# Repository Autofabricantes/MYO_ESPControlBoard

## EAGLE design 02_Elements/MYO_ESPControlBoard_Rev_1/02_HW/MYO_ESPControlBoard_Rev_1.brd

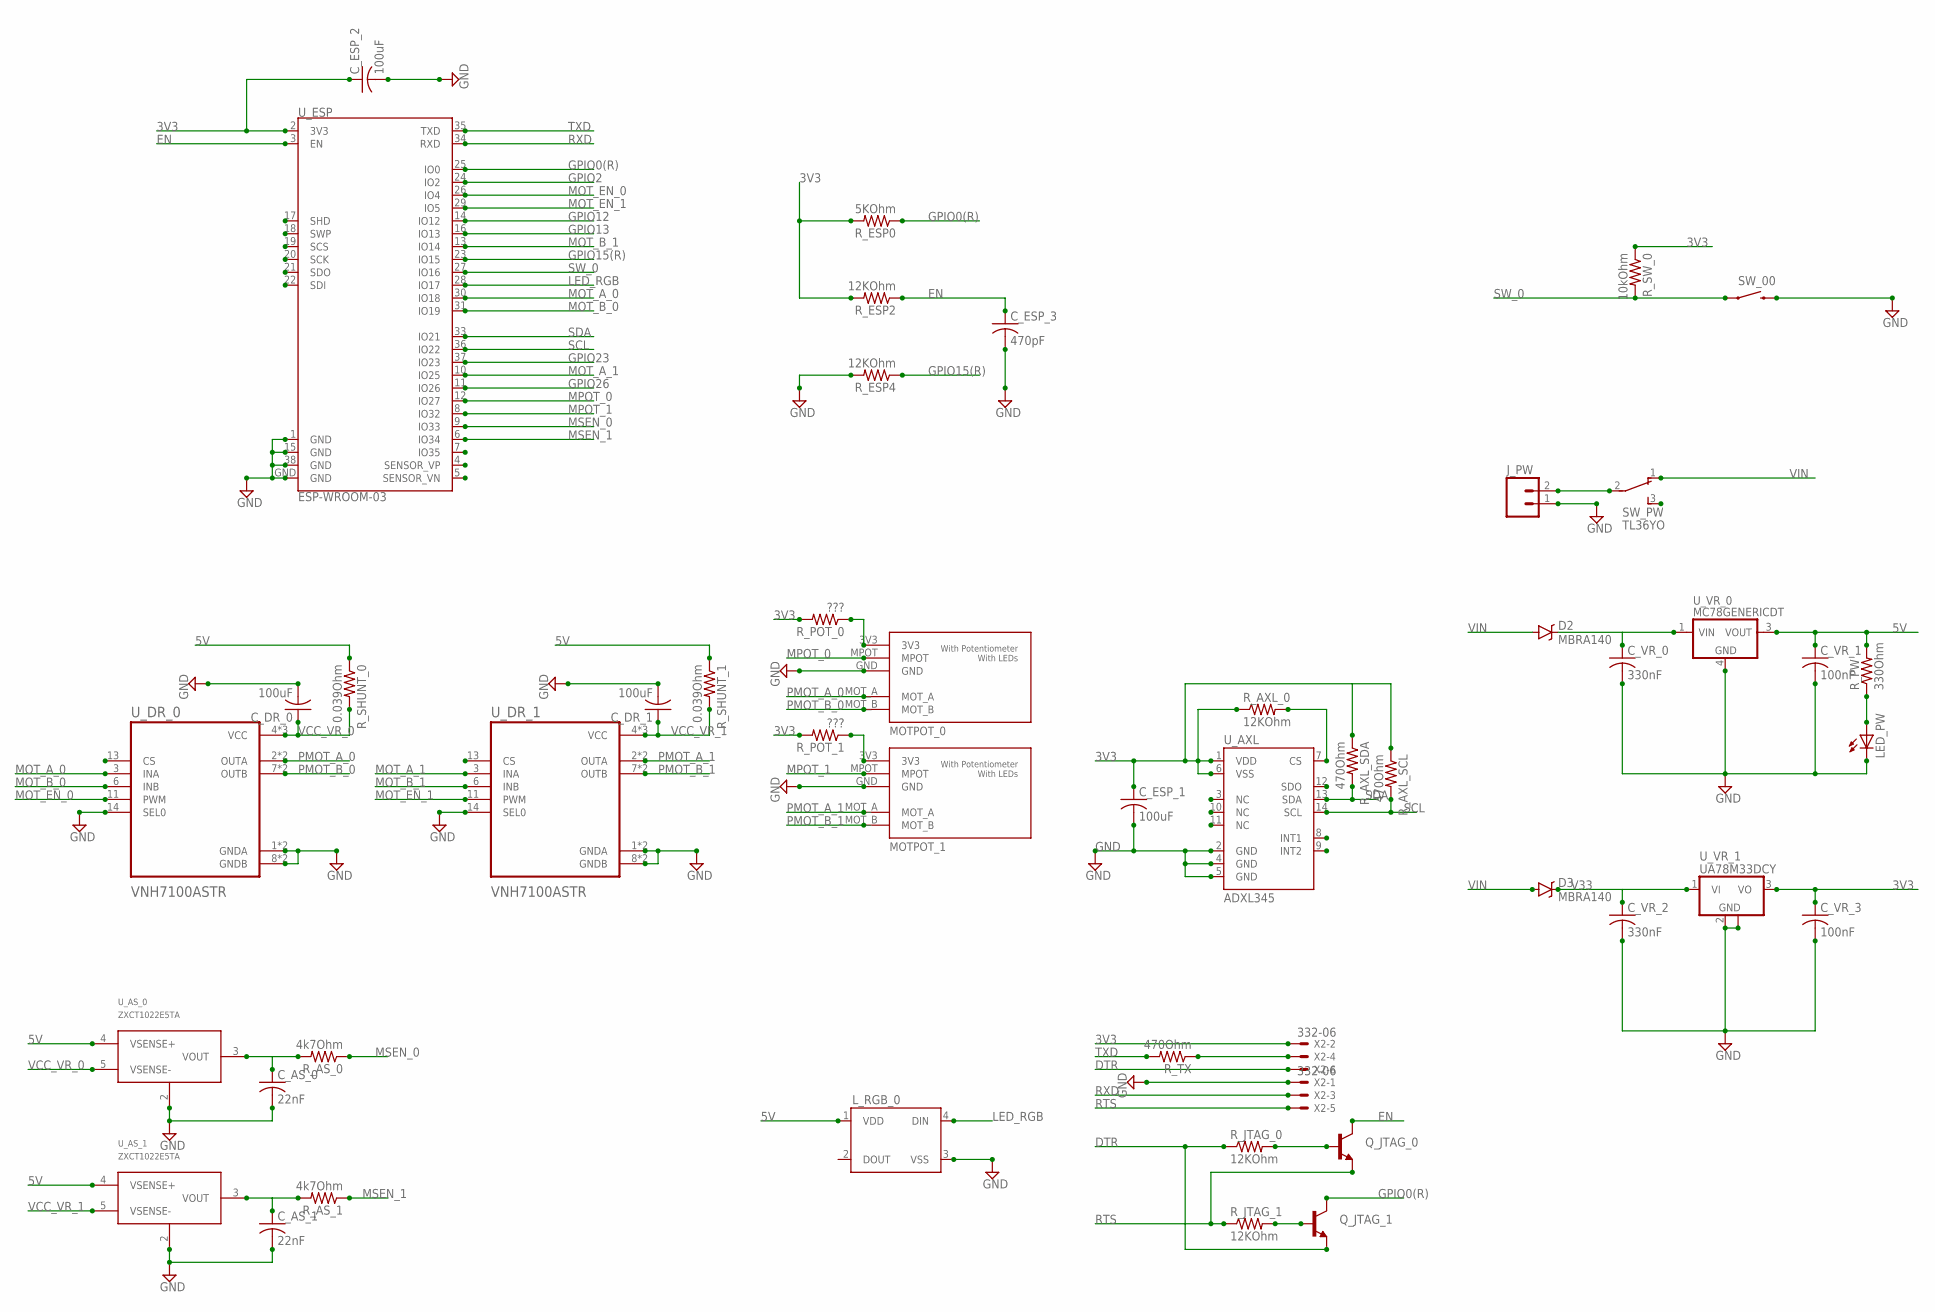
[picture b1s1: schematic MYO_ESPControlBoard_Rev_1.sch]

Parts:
C_AS_0, C_AS_1: 22nF; C0805K
C_DR_0, C_DR_1: 100uF; C0805K
C_ESP_1, C_ESP_2: 100uF; C0805K
C_ESP_3: 470pF; C0805K
C_VR_0, C_VR_2: 330nF; C0805
C_VR_1, C_VR_3: 100nF; C0805
D2, D3: MBRA140; SMA-DIODE
J_PW: M02-JST-2MM-SMT; JST-2-SMD
LED_PW: LEDSMT1206; 1206
L_RGB_0: WS2812B
MOTPOT_0, MOTPOT_1: POLOLU_MOT_POT
Q_JTAG_0, Q_JTAG_1: TRANSISTOR_NPNSOT23-3; SOT23-3
R_AS_0, R_AS_1: 4k7Ohm; M0805
R_AXL_0: 12KOhm; M0805
R_AXL_SCL: 470Ohm; M0805
R_AXL_SDA: 470Ohm; M0805
R_ESP0: 5KOhm; M0805
R_ESP2, R_ESP4: 12KOhm; M0805
R_JTAG_0, R_JTAG_1: 12KOhm; M0805
R_POT_0, R_POT_1: ???; M0805
R_PW: 330Ohm; M0805
R_SHUNT_0, R_SHUNT_1: 0.039Ohm; M0805
R_SW_0: 10kOhm; M0805
R_TX: 470Ohm; M0805
SW_00: SWITCH-MOMENTARY-2TACTILE-SWITCH-SMD-RIGHT-ANGLE; TACTILE_SWITCH-SMD-RIGHT-ANGLE
SW_PW: TL36YO; TL3XYO
U_AS_0, U_AS_1: ZXCT1022E5TA; SOT95P270X145-5N(SOT23-5)
U_AXL: ADXL345; LGA14
U_DR_0, U_DR_1: VNH7100ASTR; SOIC127P600X175-16N
U_ESP: ESP-WROOM-03
U_VR_0: MC78GENERICDT; DPAK-3
U_VR_1: UA78M33DCY; SOT223
X2: 332-06

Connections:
3V3: C_ESP_1.1, C_ESP_2.1, C_VR_3.1, R_AXL_0.1, R_AXL_SCL.1, R_AXL_SDA.1, R_ESP0.2, R_ESP2.2, R_POT_0.2, R_POT_1.2, R_SW_0.1, U_AXL.1 (VDD), U_AXL.6 (VSS), U_ESP.2 (3V3), U_VR_1.3 (VO), X2.2
5V: C_VR_1.1, L_RGB_0.1 (VDD), R_PW.2, R_SHUNT_0.1, R_SHUNT_1.1, U_AS_0.4 (VSENSE+), U_AS_1.4 (VSENSE+), U_VR_0.3 (VOUT)
DTR: Q_JTAG_1.2 (E), R_JTAG_0.1, X2.6
EN: C_ESP_3.1, Q_JTAG_0.3 (C), R_ESP2.1, U_ESP.3 (EN)
GND: C_AS_0.2, C_AS_1.2, C_DR_0.2, C_DR_1.2, C_ESP_1.2, C_ESP_2.2, C_ESP_3.2, C_VR_0.2, C_VR_1.2, C_VR_2.2, C_VR_3.2, J_PW.1, LED_PW.C, L_RGB_0.3 (VSS), MOTPOT_0.GND, MOTPOT_1.GND, R_ESP4.2, SW_00.2, U_AS_0.2 (GND), U_AS_1.2 (GND), U_AXL.2 (GND), U_AXL.4 (GND), U_AXL.5 (GND), U_DR_0.1 (GNDA), U_DR_0.8 (GNDB), U_DR_0.9 (GNDB), U_DR_0.14 (SEL0), U_DR_0.16 (GNDA), U_DR_1.1 (GNDA), U_DR_1.8 (GNDB), U_DR_1.9 (GNDB), U_DR_1.14 (SEL0), U_DR_1.16 (GNDA), U_ESP.1 (GND), U_ESP.15 (GND), U_ESP.38 (GND), U_ESP.GND, U_VR_0.4 (GND), U_VR_1.2 (GND), U_VR_1.4 (GND), X2.1
GPIO0(R): Q_JTAG_1.3 (C), R_ESP0.1, U_ESP.25 (IO0)
GPIO2: U_ESP.24 (IO2)
GPIO12: U_ESP.14 (IO12)
GPIO13: U_ESP.16 (IO13)
GPIO15(R): R_ESP4.1, U_ESP.23 (IO15)
GPIO23: U_ESP.37 (IO23)
GPIO26: U_ESP.11 (IO26)
LED_RGB: L_RGB_0.4 (DIN), U_ESP.28 (IO17)
MOT_A_0: U_DR_0.3 (INA), U_ESP.30 (IO18)
MOT_A_1: U_DR_1.3 (INA), U_ESP.10 (IO25)
MOT_B_0: U_DR_0.6 (INB), U_ESP.31 (IO19)
MOT_B_1: U_DR_1.6 (INB), U_ESP.13 (IO14)
MOT_EN_0: U_DR_0.11 (PWM), U_ESP.26 (IO4)
MOT_EN_1: U_DR_1.11 (PWM), U_ESP.29 (IO5)
MPOT_0: MOTPOT_0.MPOT, U_ESP.12 (IO27)
MPOT_1: MOTPOT_1.MPOT, U_ESP.8 (IO32)
MSEN_0: R_AS_0.1, U_ESP.9 (IO33)
MSEN_1: R_AS_1.1, U_ESP.6 (IO34)
unnamed: MOTPOT_0.3V3, R_POT_0.1
unnamed: MOTPOT_1.3V3, R_POT_1.1
unnamed: Q_JTAG_0.1 (B), R_JTAG_0.2
unnamed: LED_PW.A, R_PW.1
unnamed: Q_JTAG_1.1 (B), R_JTAG_1.2
unnamed: R_TX.1, X2.4
unnamed: C_AS_0.1, R_AS_0.2, U_AS_0.3 (VOUT)
unnamed: R_AXL_0.2, U_AXL.7 (CS)
unnamed: J_PW.2, SW_PW.2
unnamed: C_AS_1.1, R_AS_1.2, U_AS_1.3 (VOUT)
PMOT_A_0: MOTPOT_0.MOT_A, U_DR_0.2 (OUTA), U_DR_0.15 (OUTA)
PMOT_A_1: MOTPOT_1.MOT_A, U_DR_1.2 (OUTA), U_DR_1.15 (OUTA)
PMOT_B_0: MOTPOT_0.MOT_B, U_DR_0.7 (OUTB), U_DR_0.10 (OUTB)
PMOT_B_1: MOTPOT_1.MOT_B, U_DR_1.7 (OUTB), U_DR_1.10 (OUTB)
RTS: Q_JTAG_0.2 (E), R_JTAG_1.1, X2.5
RXD: U_ESP.34 (RXD), X2.3
SCL: R_AXL_SCL.2, U_AXL.14 (SCL), U_ESP.36 (IO22)
SDA: R_AXL_SDA.2, U_AXL.13 (SDA), U_ESP.33 (IO21)
SW_0: R_SW_0.2, SW_00.1, U_ESP.27 (IO16)
TXD: R_TX.2, U_ESP.35 (TXD)
V5: C_VR_0.1, D2.C, U_VR_0.1 (VIN)
V33: C_VR_2.1, D3.C, U_VR_1.1 (VI)
VCC_VR_0: C_DR_0.1, R_SHUNT_0.2, U_AS_0.5 (VSENSE-), U_DR_0.4 (VCC), U_DR_0.5 (VCC), U_DR_0.12 (VCC)
VCC_VR_1: C_DR_1.1, R_SHUNT_1.2, U_AS_1.5 (VSENSE-), U_DR_1.4 (VCC), U_DR_1.5 (VCC), U_DR_1.12 (VCC)
VIN: D2.A, D3.A, SW_PW.1 (O)

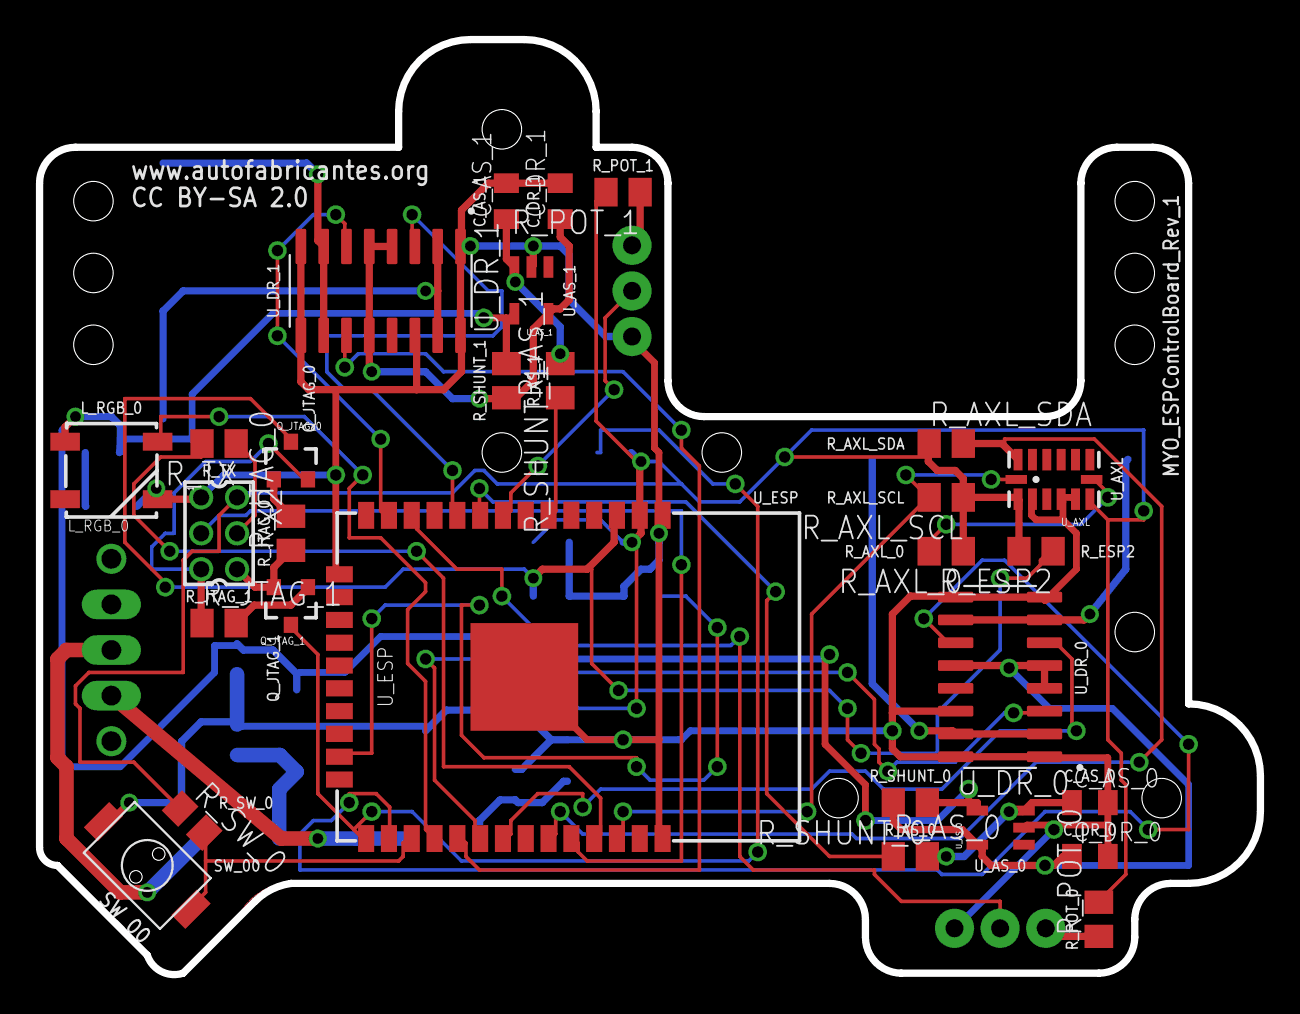
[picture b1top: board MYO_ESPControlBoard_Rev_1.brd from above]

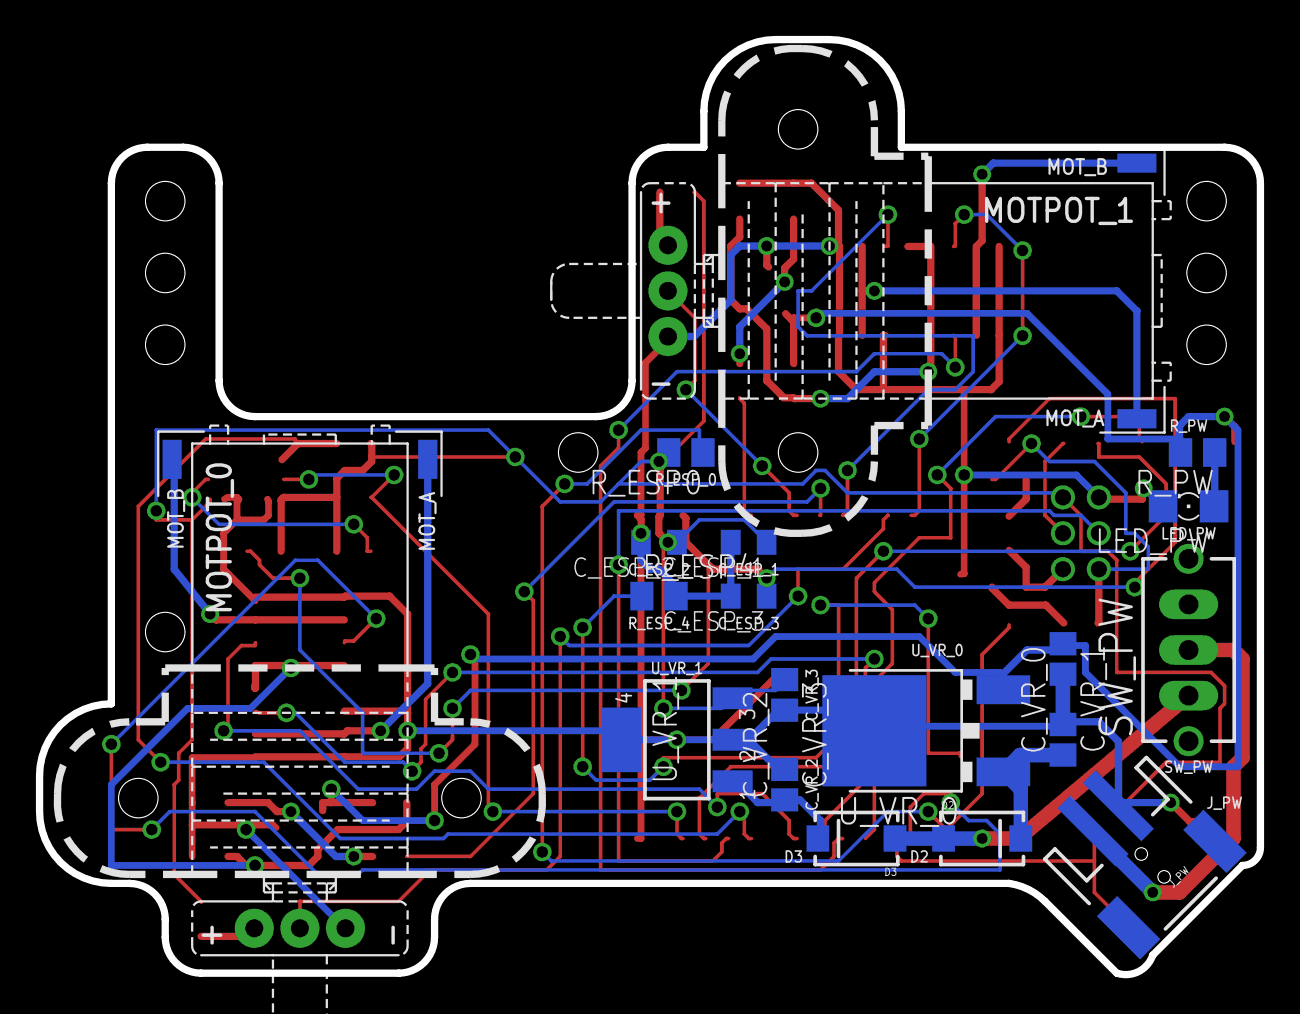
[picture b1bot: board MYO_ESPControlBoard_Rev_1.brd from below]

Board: 2 copper layers, 68.0 x 52.1 mm, 48 parts (19 on the bottom side), 43 nets.

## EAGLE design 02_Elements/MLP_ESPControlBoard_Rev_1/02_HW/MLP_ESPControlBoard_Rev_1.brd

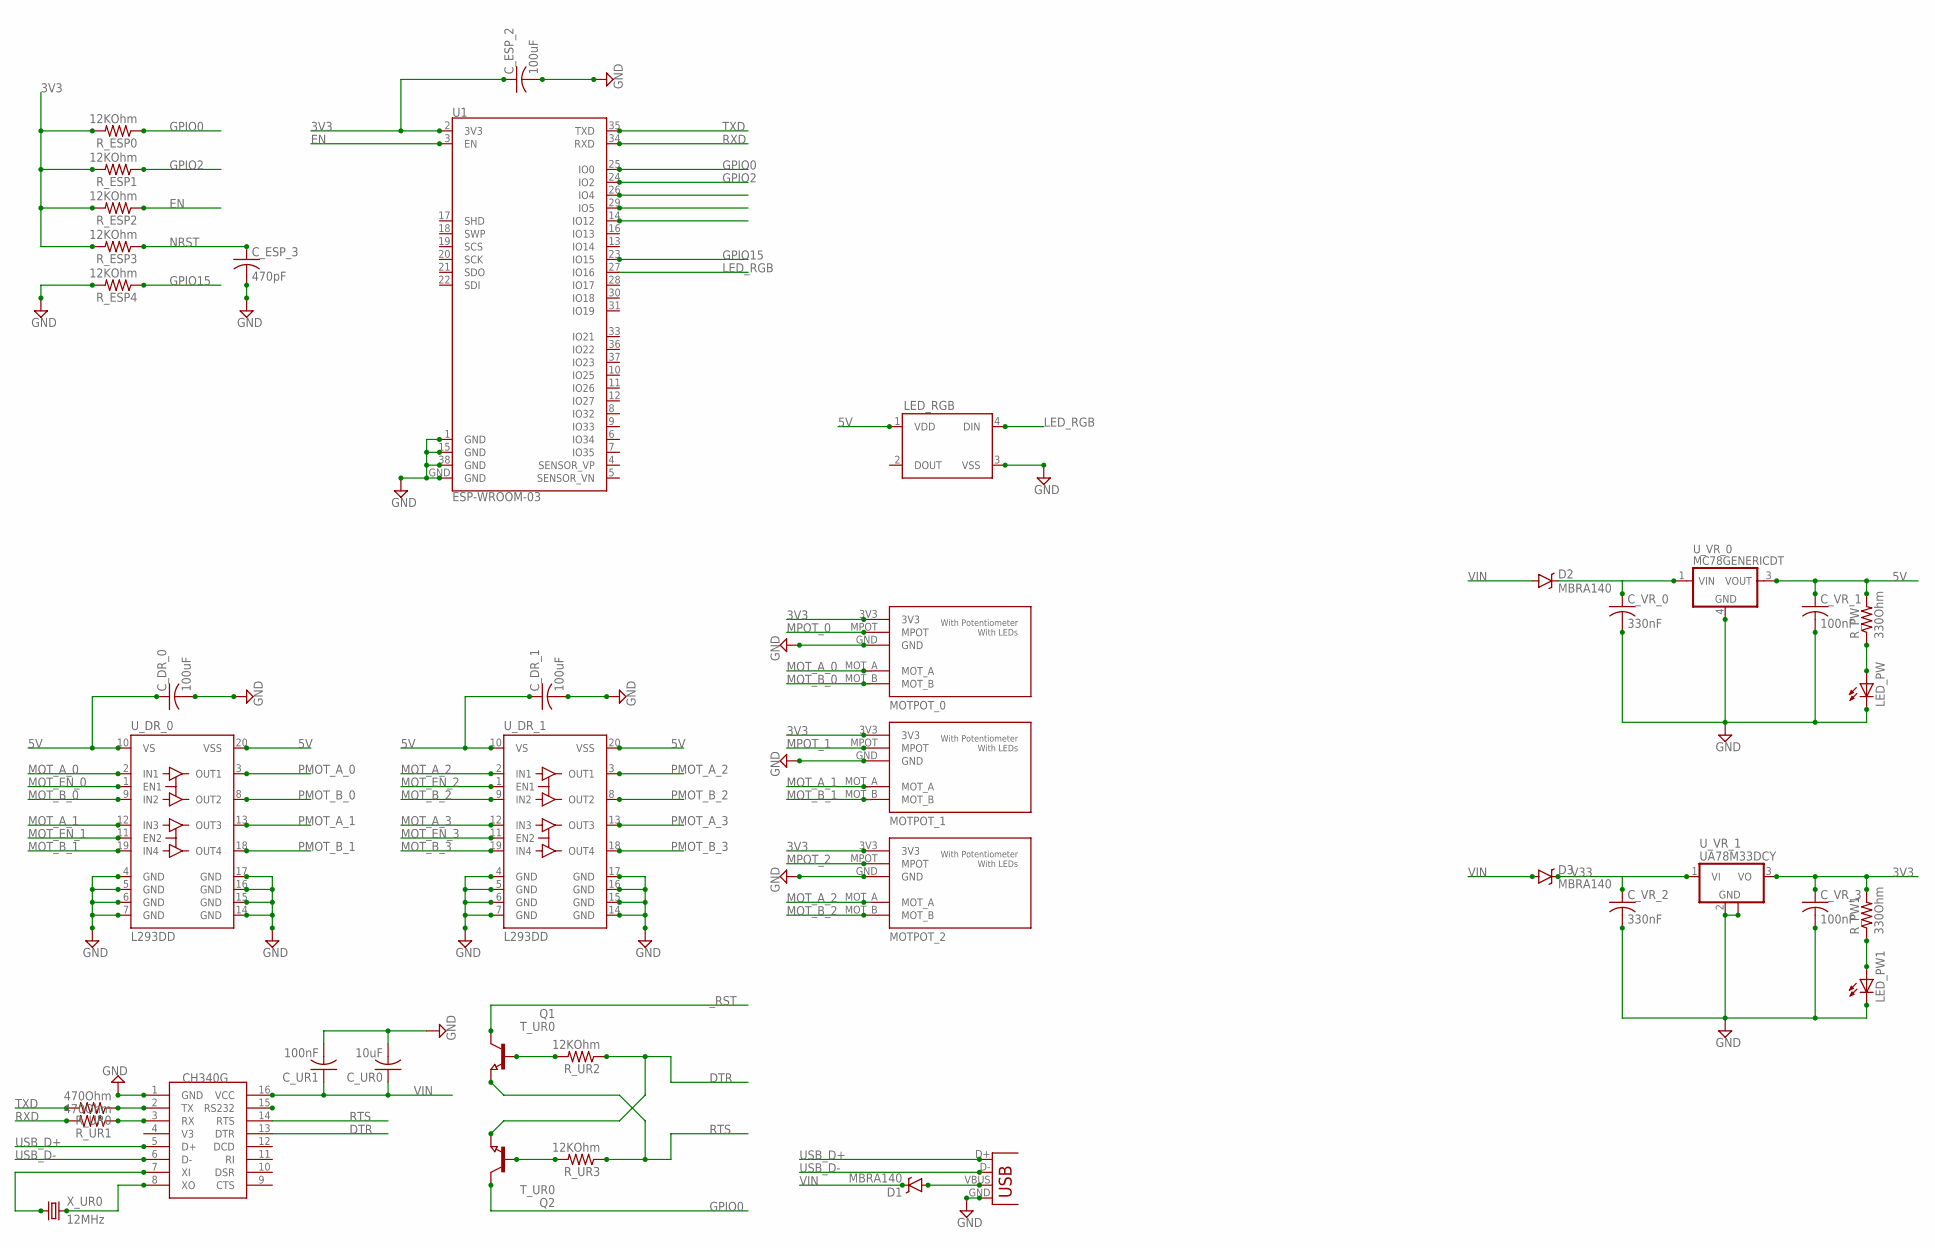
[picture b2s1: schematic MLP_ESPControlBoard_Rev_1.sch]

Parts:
C_DR_0, C_DR_1: 100uF; C0805K
C_ESP_2: 100uF; C0805K
C_ESP_3: 470pF; C0805K
C_UR0: 10uF; C0805K
C_UR1: 100nF; C0805K
C_VR_0, C_VR_2: 330nF; C1206K
C_VR_1, C_VR_3: 100nF; C1206K
D1, D2, D3: MBRA140; SMA-DIODE
LED_PW, LED_PW1: LEDSMT1206; 1206
LED_RGB: WS2812B
MOTPOT_0, MOTPOT_1, MOTPOT_2: POLOLU_MOT_POT
Q1, Q2: T_UR0; SOT23
R_ESP0, R_ESP1, R_ESP2, R_ESP3, R_ESP4: 12KOhm; M0805
R_PW, R_PW1: 330Ohm; M1206
R_UR0, R_UR1: 470Ohm; M1206
R_UR2, R_UR3: 12KOhm; M1206
U1: ESP-WROOM-03
U_DR_0, U_DR_1: L293DD; SO20
U_UR0: CH340G; SOIC16
U_VR_0: MC78GENERICDT; DPAK-3
U_VR_1: UA78M33DCY; SOT223
X1: USB-MICROB
X_UR0: 12MHz; CTS406

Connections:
3V3: C_ESP_2.1, C_VR_3.1, MOTPOT_0.3V3, MOTPOT_1.3V3, MOTPOT_2.3V3, R_ESP0.2, R_ESP1.2, R_ESP2.2, R_ESP3.2, R_PW1.2, U1.2 (3V3), U_VR_1.3 (VO)
5V: C_DR_0.1, C_DR_1.1, C_VR_1.1, LED_RGB.1 (VDD), R_PW.2, U_DR_0.10 (VS), U_DR_0.20 (VSS), U_DR_1.10 (VS), U_DR_1.20 (VSS), U_VR_0.3 (VOUT)
DTR: Q2.2 (E), R_UR2.1, U_UR0.13 (DTR)
EN: R_ESP2.1, U1.3 (EN)
GND: C_DR_0.2, C_DR_1.2, C_ESP_2.2, C_ESP_3.2, C_UR0.2, C_UR1.2, C_VR_0.2, C_VR_1.2, C_VR_2.2, C_VR_3.2, LED_PW.C, LED_PW1.C, LED_RGB.3 (VSS), MOTPOT_0.GND, MOTPOT_1.GND, MOTPOT_2.GND, R_ESP4.2, U1.1 (GND), U1.15 (GND), U1.38 (GND), U1.GND, U_DR_0.4 (GND), U_DR_0.5 (GND), U_DR_0.6 (GND), U_DR_0.7 (GND), U_DR_0.14 (GND), U_DR_0.15 (GND), U_DR_0.16 (GND), U_DR_0.17 (GND), U_DR_1.4 (GND), U_DR_1.5 (GND), U_DR_1.6 (GND), U_DR_1.7 (GND), U_DR_1.14 (GND), U_DR_1.15 (GND), U_DR_1.16 (GND), U_DR_1.17 (GND), U_UR0.1 (GND), U_VR_0.4 (GND), U_VR_1.2 (GND), U_VR_1.4 (GND), X1.GND
GPIO0: Q2.3 (C), R_ESP0.1, U1.25 (IO0)
GPIO2: R_ESP1.1, U1.24 (IO2)
GPIO15: R_ESP4.1, U1.23 (IO15)
LED_RGB: LED_RGB.4 (DIN), U1.27 (IO16)
MOT_A_0: MOTPOT_0.MOT_A, U_DR_0.2 (IN1)
MOT_A_1: MOTPOT_1.MOT_A, U_DR_0.12 (IN3)
MOT_A_2: MOTPOT_2.MOT_A, U_DR_1.2 (IN1)
MOT_A_3: U_DR_1.12 (IN3)
MOT_B_0: MOTPOT_0.MOT_B, U_DR_0.9 (IN2)
MOT_B_1: MOTPOT_1.MOT_B, U_DR_0.19 (IN4)
MOT_B_2: MOTPOT_2.MOT_B, U_DR_1.9 (IN2)
MOT_B_3: U_DR_1.19 (IN4)
MOT_EN_0: U_DR_0.1 (EN1)
MOT_EN_1: U_DR_0.11 (EN2)
MOT_EN_2: U_DR_1.1 (EN1)
MOT_EN_3: U_DR_1.11 (EN2)
MPOT_0: MOTPOT_0.MPOT
MPOT_1: MOTPOT_1.MPOT
MPOT_2: MOTPOT_2.MPOT
unnamed: Q2.1 (B), R_UR3.2
unnamed: Q1.1 (B), R_UR2.2
unnamed: LED_PW.A, R_PW.1
unnamed: U_UR0.7 (XI), X_UR0.1
unnamed: LED_PW1.A, R_PW1.1
unnamed: R_UR0.1, U_UR0.2 (TX)
unnamed: R_UR1.1, U_UR0.3 (RX)
unnamed: U_UR0.8 (XO), X_UR0.3 (2)
unnamed: D1.A, X1.VBUS
NRST: C_ESP_3.1, R_ESP3.1
PMOT_A_0: U_DR_0.3 (OUT1)
PMOT_A_1: U_DR_0.13 (OUT3)
PMOT_A_2: U_DR_1.3 (OUT1)
PMOT_A_3: U_DR_1.13 (OUT3)
PMOT_B_0: U_DR_0.8 (OUT2)
PMOT_B_1: U_DR_0.18 (OUT4)
PMOT_B_2: U_DR_1.8 (OUT2)
PMOT_B_3: U_DR_1.18 (OUT4)
RTS: Q1.2 (E), R_UR3.1, U_UR0.14 (RTS)
RXD: R_UR1.2, U1.34 (RXD)
TXD: R_UR0.2, U1.35 (TXD)
USB_D+: U_UR0.5 (D+), X1.D+
USB_D-: U_UR0.6 (D-), X1.D-
V5: C_VR_0.1, D2.C, U_VR_0.1 (VIN)
V33: C_VR_2.1, D3.C, U_VR_1.1 (VI)
VIN: C_UR0.1, C_UR1.1, D1.C, D2.A, D3.A, U_UR0.16 (VCC)
_RST: Q1.3 (C)

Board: 2 copper layers, 40 parts (0 on the bottom side), 33 nets, no tracks yet.

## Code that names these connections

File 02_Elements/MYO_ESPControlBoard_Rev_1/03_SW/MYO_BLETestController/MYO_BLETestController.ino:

/*  MYO_BLETestController
 * 
 * 
 * 
 */

#include <driver/dac.h>
#include "BluetoothSerial.h"
#include "MYO_Motor.h"
#include "MYO_LED.h"
#include <Adafruit_NeoPixel.h>
#ifdef __AVR__
 #include <avr/power.h> // Required for 16 MHz Adafruit Trinket
#endif

// Pin Definition
#define MOT_EN_0    4   // GPIO 4
#define MOT_A_0     18  // GPIO 18
#define MOT_B_0     19  // GPIO 19
#define MPOT_0      27  // GPIO 27
#define MSEN_0      33  // GPIO 33

#define MOT_EN_1    5   // GPIO 5
#define MOT_A_1     25  // GPIO 25
#define MOT_B_1     13  // GPIO 13 // GPIO14 in BRD. Changed due to Initial PWM Signal during BOOT
#define MPOT_1      32  // GPIO 32
#define MSEN_1      34  // GPIO 34

#define SW_0        16  // GPIO 16

#define LED_RGB     17  // GPIO17

BluetoothSerial SerialBT;
MYO_LED   LED(LED_RGB);
MYO_Motor MOT_0(MOT_EN_0, MOT_A_0, MOT_B_0, MPOT_0, MSEN_0);
MYO_Motor MOT_1(MOT_EN_1, MOT_A_1, MOT_B_1, MPOT_1, MSEN_1);

void readSerialCommand(){
    if (SerialBT.available()) {
      //String value =  SerialBT.read());
      String serialMessage = SerialBT.readString();
      if (serialMessage.length() > 0) {
        SerialBT.print("CMD Recieved: ");
        for (int i = 0; i < serialMessage.length(); i++){
          SerialBT.print(serialMessage[i]);
          
        }
        //SerialBT.println("");
        if(((serialMessage[0] == 'A')||(serialMessage[0] == 'B')) && (serialMessage.length()==7)){
          if(serialMessage[1] == 'P'){
            readCommandForMotorPosition(serialMessage);
          }else if(serialMessage[1] == 'S'){
            readCommandForMotorSpeed(serialMessage);
          }  
        }else if(serialMessage.substring(0,4).equals("STOP")){
          LED.fadeColor(BLUE_LOW, BLUE_HIGH, 500);
          MOT_0.stopLiberate();
          MOT_1.stopLiberate();
          LED.fadeColor(BLUE_LOW, BLUE_HIGH, 500);
        }else{
          SerialBT.println("Message Not Supported");
          LED.fadeColor(RED_LOW, RED_HIGH, 500);
        }
      }
    }
};

void setup() {
  LED.init();
  LED.setColor(CYAN_LOW);
  MOT_0.stopLiberate();
  MOT_1.stopLiberate();
  MOT_0.goToPosition(5);
  MOT_1.goToPosition(5);
  
  Serial.begin(9600); 
  SerialBT.begin("MYO_ATF"); //Bluetooth device name
  Serial.println("Waiting a client connection to notify...");
}

void loop() {
  // put your main code here, to run repeatedly:
  readSerialCommand();
  delay(10);
}

void readCommandForMotorPosition(String serialMessage){
  // First Check the message is correct (supported values between 0 and 100
  if(((serialMessage[2]== '0') || (serialMessage[2]== '1')) &&
     (((serialMessage[3]>= '0') && (serialMessage[3] <= '9')) &&
     ((serialMessage[4]>= '0') && (serialMessage[4] <= '9')))){
        int aimedPosition = (serialMessage[2] - 48)*100 + (serialMessage[3] - 48)*10 + (serialMessage[4] - 48)*1;
        if(aimedPosition > 100){
          aimedPosition = 100;
        }
        if(serialMessage[0] == 'A'){
          SerialBT.print("Motor A to position: ");
          SerialBT.println(aimedPosition);
          LED.fadeColor(BLUE_LOW, BLUE_HIGH, 500);
          MOT_0.goToPosition(map(aimedPosition, 0, 100, 5, 95));
        }else{
          SerialBT.print("Motor B to position: ");
          SerialBT.println(aimedPosition);
          LED.fadeColor(BLUE_LOW, BLUE_HIGH, 500);
          MOT_1.goToPosition(map(aimedPosition, 0, 100, 5, 95));
        }
  }else{
    SerialBT.print("Serial Message Incorrect: ");
    SerialBT.print(serialMessage);
    SerialBT.println(" .Use a notation with APXXX o BPXXX with values 000-100");
    LED.fadeColor(RED_LOW, RED_HIGH, 500);
  }
}

void readCommandForMotorSpeed(String serialMessage){
    // First Check the message is correct (supported values between 0 and 100
  if(((serialMessage[2]== '0') || (serialMessage[2]== '1')) &&
     (((serialMessage[3]>= '0') && (serialMessage[3] <= '9')) &&
     ((serialMessage[4]>= '0') && (serialMessage[4] <= '9')))){
        int aimedSpeed = (serialMessage[2] - 48)*100 + (serialMessage[3] - 48)*10 + (serialMessage[4] - 48)*1;
        if(aimedSpeed > 100){
          aimedSpeed = 100;
        }
        if(serialMessage[0] == 'A'){
          SerialBT.print("Motor A to speed: ");
          SerialBT.println(aimedSpeed);
          LED.fadeColor(TURQOUISE_LOW, TURQOUISE_HIGH, 500);
          MOT_0.setMotorSpeed(aimedSpeed);
        }else{
          SerialBT.print("Motor B to speed: ");
          SerialBT.println(aimedSpeed);
          LED.fadeColor(TURQOUISE_LOW, TURQOUISE_HIGH, 500);
          MOT_1.setMotorSpeed(aimedSpeed);
        }
  }else{
    SerialBT.print("Serial Message Incorrect: ");
    SerialBT.print(serialMessage);
    SerialBT.println(" .Use a notation with ASXXX o BSXXX with values 000-100");
    LED.fadeColor(RED_LOW, RED_HIGH, 500);
  }
}

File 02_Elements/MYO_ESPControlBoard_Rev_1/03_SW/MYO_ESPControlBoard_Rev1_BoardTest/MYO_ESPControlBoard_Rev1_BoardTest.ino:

#include <Adafruit_NeoPixel.h>

// Pin Definition
const int pMOT_EN_0     = 4;
const int pMOT_A_0      = 18;
const int pMOT_B_0      = 19;
const int pMPOT_0       = 27;

const int pMOT_EN_1     = 5;
const int pMOT_A_1      = 25;
const int pMOT_B_1      = 14;
const int pMPOT_1       = 32;

const int pMSEN_0       = 12;
const int pMSEN_1       = 33;

const int pLED_RGB      = 17;

const int pSW_0         = 16;

const int pSDA          = 21;
const int pSCL          = 22;


Adafruit_NeoPixel ledRGB = Adafruit_NeoPixel(1, pLED_RGB, NEO_RGB + NEO_KHZ800);

//Adafruit_NeoPixel pixels = Adafruit_NeoPixel(1, pLED_RGB, NEO_GRB + NEO_KHZ800);

bool memorySW = false;

void setup() {
  Serial.begin(115200);
  ledRGB.begin();
  ledRGB.setPixelColor(0, 255, 0, 255); // Moderately bright green color.
  ledRGB.show(); // This sends the updated pixel color to the hardware.
  delay(500); // Delay for a period of time (in milliseconds).
  pinMode(pMOT_EN_0,  OUTPUT);
  pinMode(pMOT_A_0,   OUTPUT);
  pinMode(pMOT_B_0,   OUTPUT);
  pinMode(pMOT_EN_1,  OUTPUT);
  pinMode(pMOT_A_1,   OUTPUT);
  pinMode(pMOT_B_1,   OUTPUT);
  pinMode(pSW_0,      INPUT);
  digitalWrite(pMOT_EN_0,  LOW);
  digitalWrite(pMOT_A_0,  LOW);
  digitalWrite(pMOT_B_0,  LOW);
  digitalWrite(pMOT_EN_1,  LOW);
  digitalWrite(pMOT_A_1,  LOW);
  digitalWrite(pMOT_B_1,  LOW);

}

void loop() {
  if(swActiveMomentary()){
    Serial.println("");
    Serial.println("PUSH!");
    ledRGB.setPixelColor(0, random(0,100), random(0,100), random(0,100)); // Moderately bright green color.
  }
  Serial.print(".");
  ledRGB.show(); // This sends the updated pixel color to the hardware.
  delay(10);
}

bool swActiveMomentary(){
  bool newSW = digitalRead(pSW_0);
  if((memorySW)&&(!newSW)){
    memorySW = newSW;
    return true;
  }else{
    memorySW = newSW;
    return false;
  }
}

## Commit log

2018-10-22 First Setup Folder
    First Simple Setup of the folder structure
2018-12-01 Beginning of Schematic Design
    Just temporary backup with circuits:
    - ESP32
    - Serial USB Comm
2019-01-23 Schematic Update
    Advanced Schematic, not final
2019-01-30 MYO_ESPControlBoard_Rev_1 Schematic completed
    Upload of the MYO_ESPControlBoard_Rev_1 Schematic to be tested
2021-01-24 MYO_ESPControlBoard_Rev_1 Draft Update on HW (SCH, BRD and 3D)
    Primary Draft of the PCB Schematic and Layout of MYO_ESPControlBoard_Rev_1, for evaluation:
    - Complete Schematic
    - Draft Layout without Drills or Silk
    - Primary 3D Model
2021-02-02 Updated Design with NPN JTAG Programming Interface
    Changed Schematic:
    - Added NPN JTAG Controller (as for https://dl.espressif.com/dl/schematics/ESP32-Core-Board-V2_sch.pdf ). Suppresed 2 Tactile Switches for Programming Interface
    - Added 1 Tactile Switch for User Interface
    - Added Expressiv Documentation
2021-02-04 MYO_ESPControlBoard_Rev_1 Schematic Fixed. New Dimensions for Board
    MYO_ESPControlBoard_Rev_1:
    - Schematic Fixed
    - Tactile Switch SW_1 Removed
    - New Dimensions and Board Layout
    Transition Commit, soon to be finished :-)
2021-02-09 Updated Schematic and Board
    Safe Bakcup
2021-02-14 Initial version
2021-02-19 Updated Dimension and Layout MYO_ESPControlBoard_Rev_1
    Changes on MYO_ESPControlBoard_Rev_1:
    - New Dimensions and Layout
    - Changed Motor + Bracket Footprint
    - Changed User Tactile Switch
    - Added BOM in .txt format
2021-02-21 MYO_ESPControlBoard_Rev_1 Final revision and Gerber Files
    MYO_ESPControlBoard_Rev_1:
    - Finished Silk Serigraphy
    - Generated new 3D Model EagleUp ULP
    - Generated Gerber Files
2021-04-03 Initial integration
2021-04-04 Update State and transition class object. Update constats header file.
2021-04-19 Added MYO_ESPControlBoard_Rev_1_BoardTest.ino
    Added MYO_ESPControlBoard_Rev_1_BoardTest.ino with a test SW for the board connections.
2021-04-25 Cleaning code and update
    - Deletion of mitten references (cleaning code).
    - Deletion of logging (use of espresiff libraries).
    - deletion of state and transition classes (change of code design).
    - Deletion of OTA and web server configuration (to use in latter versions).
2021-05-06 Integration of Myo armband communication libraries
2021-06-06 Update. OTA & Threading
2021-06-07 update OTA code
2021-09-19 3D Models updated
2021-09-21 MYO_BLETestController.ino
    Added code to test the board regarding mechanical issues. It covers:
    - BLE Control trhough an Android BLE Terminal (Not IOS pls)
    - MYO_Motor.h for Motor Control
    - MYO_LED.h for RGB LED Control
    TODO:
    - Fix initialization GPIO for MOT_B_1
2021-09-21 Corrected MYO_Motor::setDirection()
    That's right! This is good news don't you now?
2021-09-27 Finished MYO_BLETestController.ino
    Added the following instructions:
    - AP000 - AP100, BP000 to BP100 to control Position
    - AS000 - AS100, BS000 to BS100 to control Speed
    - STOP to STOP Liberate
2021-10-03 Corrección de errores OTA
    Se había intentado mantener dos hilos simultaneos, uno manteniendo el webserver en pie para la carga del código OTA y otro para la ejecución del código principal, pero terminábamos teniendo un crash 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
2022-08-26 Update with BOM and correct Pinout
    Update with BOM and correct Pinout due to ESP32 GPIO14 PWM during boot.

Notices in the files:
02_Elements/MLP_ESPControlBoard_Rev_1/02_HW/MLP_ESPControlBoard_Rev_1.brd:
CC BY-SA 3.0
02_Elements/MYO_ESPControlBoard_Rev_1/02_HW/MYO_ESPControlBoard_Rev_1.brd:
CC BY-SA 2.0
parts and their libraries:
SparkFun: Licensing: CC v3.0 Share-Alike You are welcome to use this library for commercial purposes.
SparkFun-DiscreteSemi: Licensing: Creative Commons ShareAlike 4.0 International - https://creativecommons.org/licenses/by-sa/4.0
